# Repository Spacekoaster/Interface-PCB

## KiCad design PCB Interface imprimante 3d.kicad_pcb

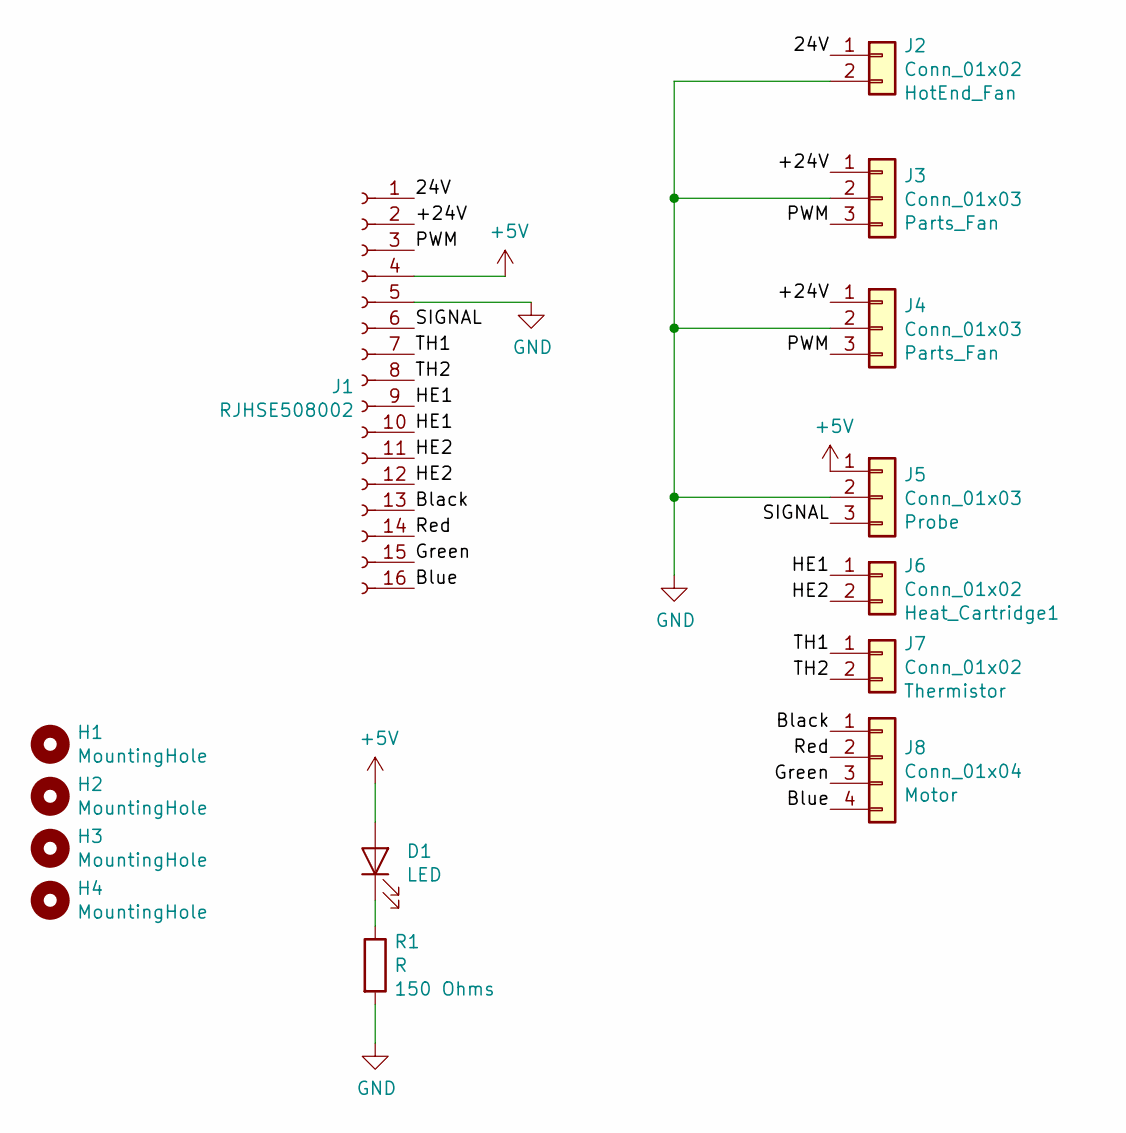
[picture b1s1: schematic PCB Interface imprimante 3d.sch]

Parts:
D1: LED; LED_1206_3216Metric_Pad1.42x1.75mm_HandSolder
H1, H2, H3, H4: MountingHole; MountingHole_3.2mm_M3
J1: RJHSE508002
J2, J6, J7: Conn_01x02; JST_XH_B2B-XH-A_1x02_P2.50mm_Vertical
J3, J4, J5: Conn_01x03; JST_XH_B3B-XH-A_1x03_P2.50mm_Vertical
J8: Conn_01x04; JST_XH_B4B-XH-A_1x04_P2.50mm_Vertical
R1: R; R_1206_3216Metric_Pad1.42x1.75mm_HandSolder

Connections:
+5V: D1.2 (A), J1.4, J5.1
/24V: J1.1, J2.1
/+24V: J1.2, J3.1, J4.1
/Black: J1.13, J8.1
/Blue: J1.16, J8.4
/Green: J1.15, J8.3
/HE1: J1.9, J1.10, J6.1
/HE2: J1.11, J1.12, J6.2
/PWM: J1.3, J3.3, J4.3
/Red: J1.14, J8.2
/SIGNAL: J1.6, J5.3
/TH1: J1.7, J7.1
/TH2: J1.8, J7.2
GND: J1.5, J2.2, J3.2, J4.2, J5.2, R1.2
unnamed: D1.1 (K), R1.1

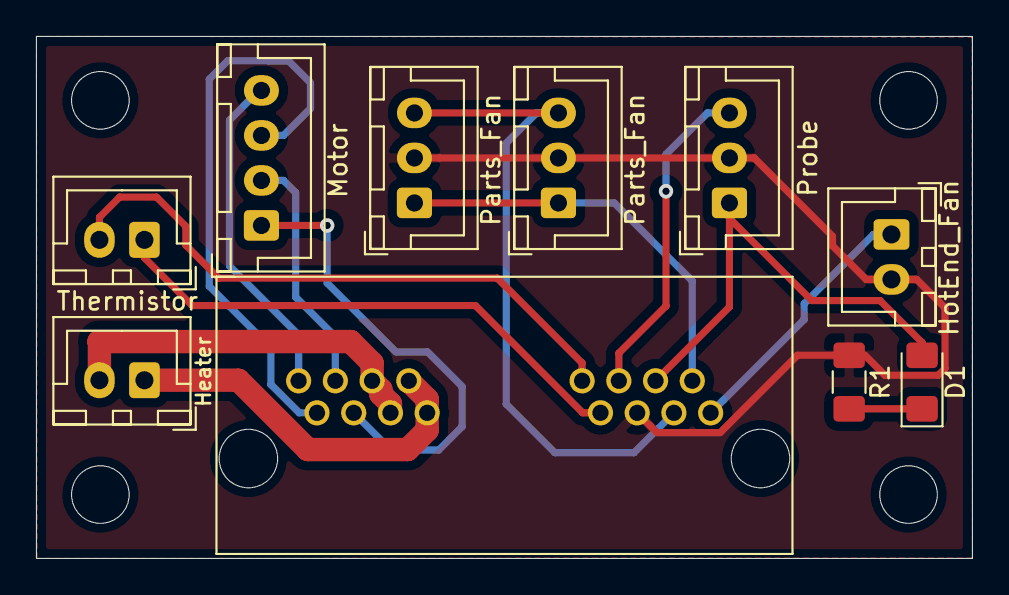
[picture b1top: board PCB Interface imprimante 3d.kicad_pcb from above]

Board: 2 copper layers, 52.0 x 29.0 mm, 14 parts (0 on the bottom side), 15 nets.

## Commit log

2020-08-17 V1
    First version of the PCB. Be careful, there're small errors.
2020-08-17 Added BOM
    BOM with components ordered from Digikey
